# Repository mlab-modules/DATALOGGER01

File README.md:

# DATALOGGER01 - MLAB's Versatile processor module

The DATALOGGER01 is a versatile electronic module designed by MLAB, containing an ATmega1284p processor. The module is programmable in the Arduino IDE and compatible with a variety of development environments and programming languages.

One of the significant features of this module is an SD card slot, a convenient provision for data logging from the processor. With a built-in battery holder, the module ensures uninterrupted operation without reliance on an external power supply.

The DATALOGGER01 exhibits a range of applications, thanks to its I2C, UART, ADC input, and GPIO pins. Additionally, it's furnished with a power switch to effectively manage power consumption of connected devices.

Setting it apart, the module includes an EEPROM AT23CS64, containing a unique serial number to distinguish logs from different DATALOGGER01-based devices. Moreover, it comprises a PCF85263 RTC circuit, with the option to connect a backup battery.

## Key Features:
- **Processor:** [ATmega1284p](https://en.wikipedia.org/wiki/Atmel_AVR#ATmega)
- **Interoperability:** Compatibility with Arduino and supports a range of other development platforms and programming languages.
- **Data Logging:** An SD Card Slot for extensive data storage.
- **Power Management:** Self-sufficient with an integrated battery holder.
- **Connectivity Options:** Diverse interfacing options with I2C, UART, ADC input, and GPIO pins.
- **Energy Efficiency:** Onboard power switch for managing external devices' power consumption.
- **Unique Identification:** Inbuilt [EEPROM AT23CS64](https://www.mouser.com/datasheet/2/268/doc0180-1353557.pdf) with a unique serial number.
- **Real-Time Tracking:** Inclusion of a [PCF85263](https://www.nxp.com/docs/en/data-sheet/PCF85263A.pdf) RTC circuit with backup battery connectivity.

## Potential Use Cases:
- **Data Collection:** Can collect, store, and analyze data from various sensors and devices.
- **Remote Monitoring:** Can be incorporated into IoT systems for remote data collection and monitoring.
- **Autonomous Systems:** Suitable for devices needing independent functioning.
- **Space Research:** Applicable as data loggers and locator devices for stratospheric balloons.

## In Action:
- The DATALOGGER01 module has proven its efficacy in:
   - **[GEODOS01](https://www.ust.cz/UST-dosimeters/GEODOS/)**: A fully autonomous scintillation detector incorporating LoRa IoT, operating without human intervention.
   - **FÍK stratospherics balloons Avionics**: DATALOGGER1 played a important role as a data logger and locator in the stratospheric balloons' avionics organized by [ODZ ÚJF](http://www.ujf.cas.cz/cs/oddeleni/oddeleni-dozimetrie-zareni/vyzkum/lety-fik/).

## Schematics

## Useful Links:
- [ATmega1284p](https://en.wikipedia.org/wiki/Atmel_AVR#ATmega) - Wikipedia
- [ARDUINO Programming Environment](https://www.arduino.cc/) - Official Arduino Site
- [EEPROM AT23CS64](https://www.mouser.com/datasheet/2/268/doc0180-1353557.pdf) - Mouser Electronics
- [PCF85263](https://www.nxp.com/docs/en/data-sheet/PCF85263A.pdf) - NXP Semiconductors

Discover the potential of DATALOGGER01 module and utilize it for your projects!

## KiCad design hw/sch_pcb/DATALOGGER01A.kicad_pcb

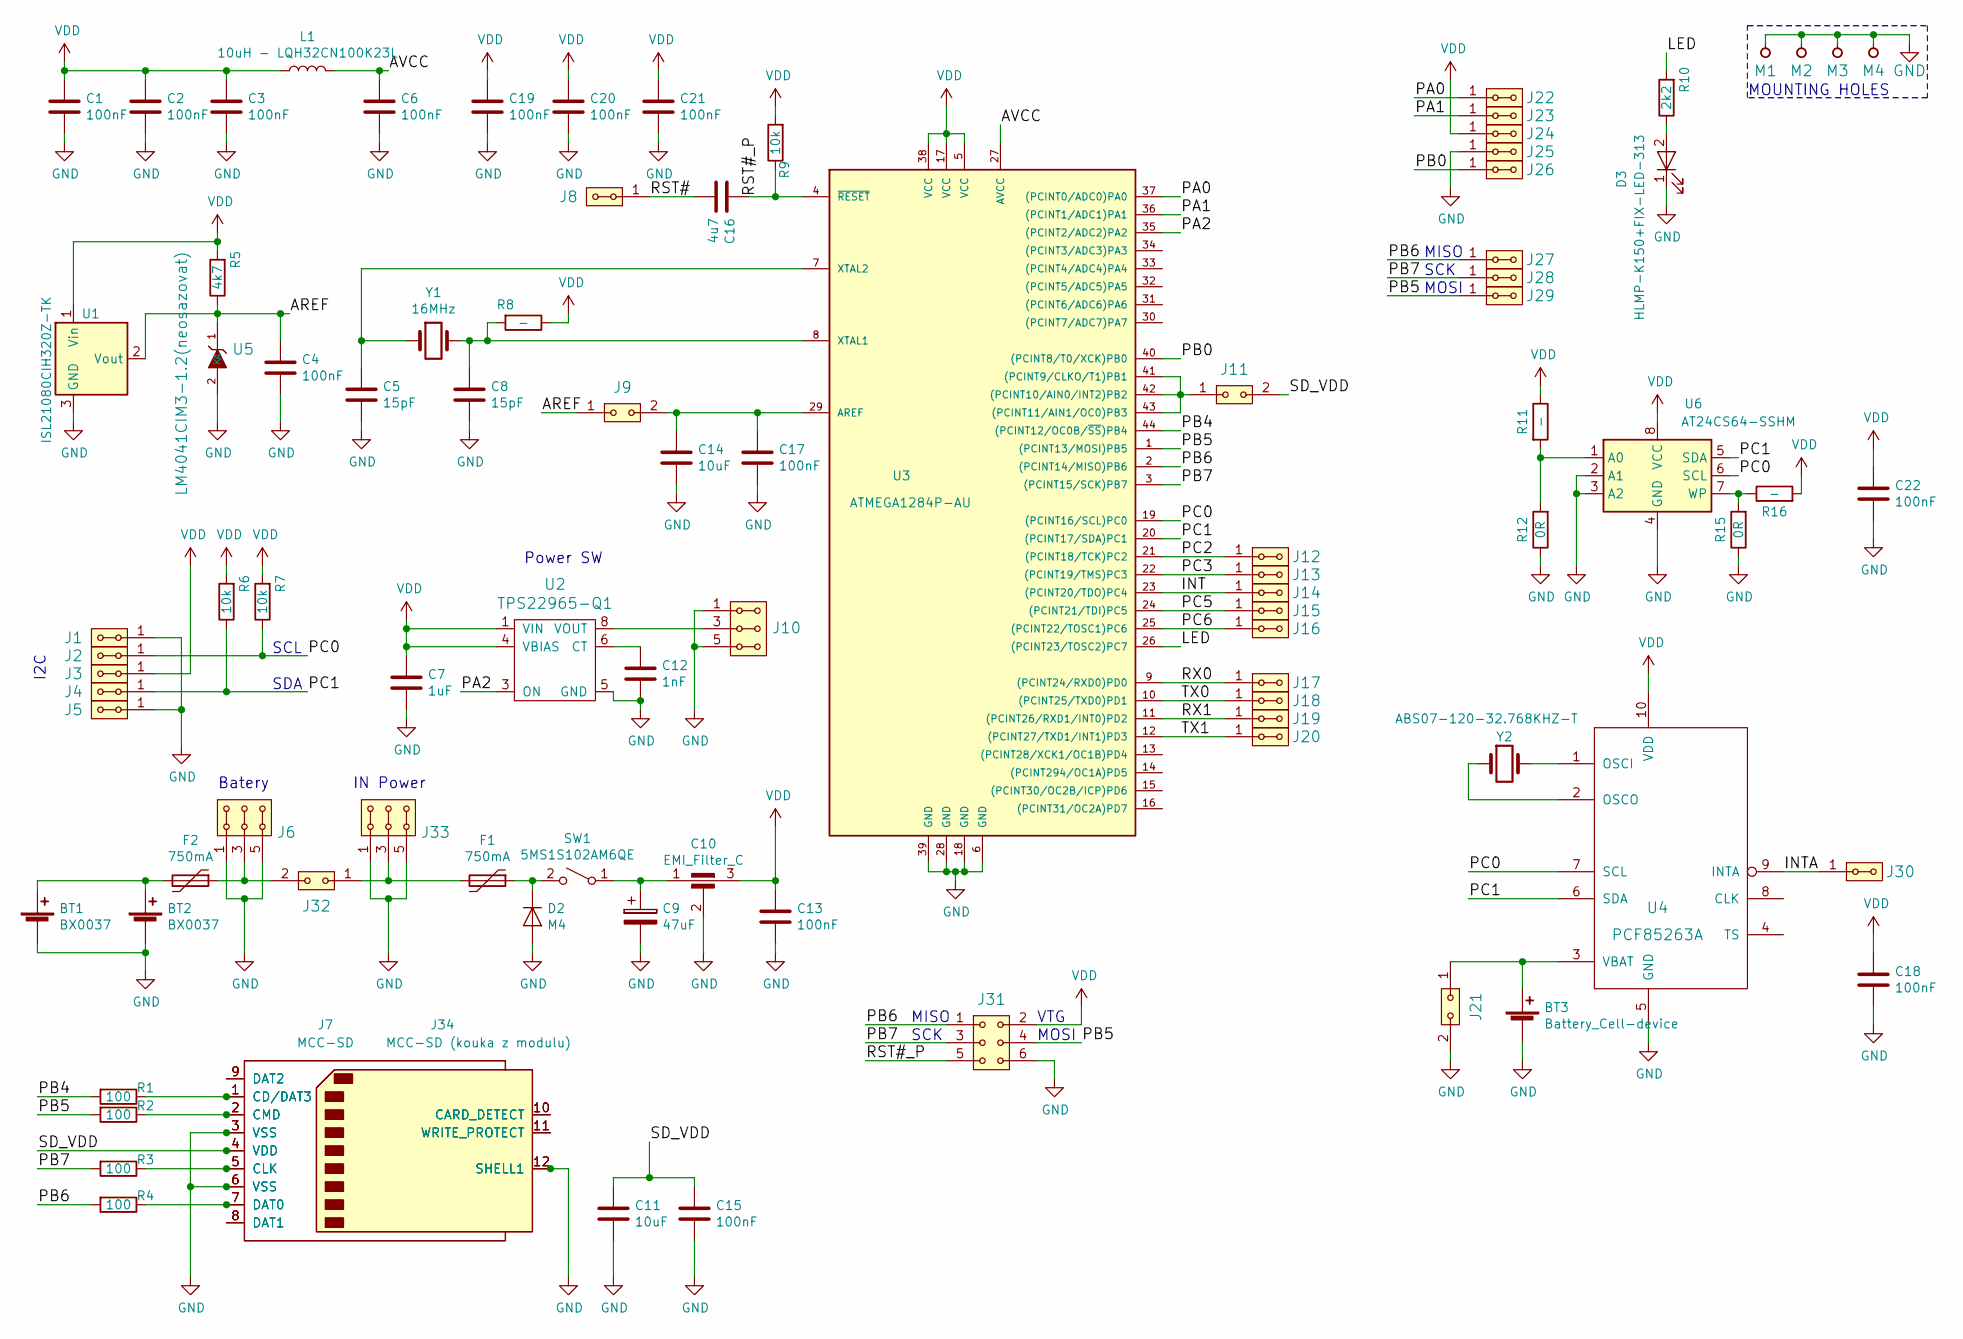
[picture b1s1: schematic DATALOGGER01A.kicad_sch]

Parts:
BT1, BT2: BX0037
BT3: Battery_Cell-device; CH28-2032
C1, C2, C3, C4, C6, C13, C15, C17, C18, C19, C20, C21, C22: 100nF; SMD-0805
C5, C8: 15pF; SMD-0805
C7: 1uF; SMD-0805
C9: 47uF; TantalC_SizeC_Reflow
C10: EMI_Filter_C; FIR1
C11, C14: 10uF; SMD-0805
C12: 1nF; SMD-0805
C16: 4u7; SMD-0805
D2: M4; SMA_Standard
D3: HLMP-K150+FIX-LED-313; FIX-LED-313
F1, F2: 750mA; 1812
J1, J2, J3, J4, J5, J8, J12, J13, J14, J15, J16, J17, J18, J19, J20, J22, J23, J24, J25, J26, J27, J28, J29, J30: HEADER_2x01_PARALLEL; Straight_2x01
J6, J10, J33: HEADER_2x03_PARALLEL; Straight_2x03
J7: MCC-SD; SD_TE_2041021
J9, J11, J21, J32: HEADER_2x01; Straight_2x01
J31: HEADER_2x03; Straight_2x03
J34: MCC-SD (kouka z modulu); MCC-SD
L1: 10uH - LQH32CN100K23L; SMD-1210
M1, M2, M3, M4: HOLE; MountingHole_3mm
R1, R2, R3, R4: 100; SMD-0805
R5: 4k7; SMD-0805
R6, R7, R9: 10k; SMD-0805
R8, R11, R16: -; SMD-0805
R10: 2k2; SMD-0805
R12, R15: 0R; SMD-0805
SW1: 5MS1S102AM6QE
U1: ISL21080CIH320Z-TK; SOT-23
U2: TPS22965-Q1; WSON-8-1EP_2x2mm_P0.5mm_EP0.9x1.6mm_ThermalVias
U3: ATMEGA1284P-AU; TQFP-44_10x10mm_P0.8mm
U4: PCF85263A; TSSOP-10_3x3mm_Pitch0.5mm
U5: LM4041CIM3-1.2(neosazovat); SOT-23
U6: AT24CS64-SSHM; SOIC-8_3.9x4.9mm_P1.27mm
Y1: 16MHz; Crystal_HC49-U_Vertical
Y2: ABS07-120-32.768KHZ-T; ABS07

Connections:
/AREF: C4.1, J9.1, R5.1, U1.2 (Vout), U5.1 (K)
/AVCC: C6.1, L1.2, U3.27 (AVCC)
/INT: J14.1, J14.2, U3.23 ((PCINT20/TDO)PC4)
/INTA: J30.1, J30.2, U4.9 (INTA)
/LED: R10.2, U3.26 ((PCINT23/TOSC2)PC7)
/PA0: J22.1, J22.2, U3.37 ((PCINT0/ADC0)PA0)
/PA1: J23.1, J23.2, U3.36 ((PCINT1/ADC1)PA1)
/PA2: U2.3 (ON), U3.35 ((PCINT2/ADC2)PA2)
/PB0: J26.1, J26.2, U3.40 ((PCINT8/T0/XCK)PB0)
/PB4: R1.2, U3.44 ((PCINT12/OC0B/~SS)PB4)
/PB5: J29.1, J29.2, J31.4, R2.2, U3.1 ((PCINT13/MOSI)PB5)
/PB6: J27.1, J27.2, J31.1, R4.2, U3.2 ((PCINT14/MISO)PB6)
/PB7: J28.1, J28.2, J31.3, R3.2, U3.3 ((PCINT15/SCK)PB7)
/PC0: J2.1, J2.2, R7.1, U3.19 ((PCINT16/SCL)PC0), U4.7 (SCL), U6.6 (SCL)
/PC1: J4.1, J4.2, R6.1, U3.20 ((PCINT17/SDA)PC1), U4.6 (SDA), U6.5 (SDA)
/PC2: J12.1, J12.2, U3.21 ((PCINT18/TCK)PC2)
/PC3: J13.1, J13.2, U3.22 ((PCINT19/TMS)PC3)
/PC5: J15.1, J15.2, U3.24 ((PCINT21/TDI)PC5)
/PC6: J16.1, J16.2, U3.25 ((PCINT22/TOSC1)PC6)
/RST#: C16.2, J8.1, J8.2
/RST#_P: C16.1, J31.5, R9.1, U3.4 (~RESET)
/RX0: J17.1, J17.2, U3.9 ((PCINT24/RXD0)PD0)
/RX1: J19.1, J19.2, U3.11 ((PCINT26/RXD1/INT0)PD2)
/SD_VDD: C11.1, C15.1, J7.4 (VDD), J11.2, J34.4 (VDD)
/TX0: J18.1, J18.2, U3.10 ((PCINT25/TXD0)PD1)
/TX1: J20.1, J20.2, U3.12 ((PCINT27/TXD1/INT1)PD3)
GND: BT1.2 (-), BT2.2 (-), BT3.2 (-), C1.2, C2.2, C3.2, C4.2, C5.2, C6.2, C7.2, C8.2, C9.2, C10.2, C11.2, C12.2, C13.2, C14.2, C15.2, C17.2, C18.2, C19.2, C20.2, C21.2, C22.2, D2.2 (A), D3.1 (K), J1.1, J1.2, J5.1, J5.2, J6.1, J6.2, J6.5, J6.6, J7.3 (VSS), J7.6 (VSS), J7.12 (SHELL1), J10.1, J10.2, J10.5, J10.6, J21.2, J25.1, J25.2, J31.6, J33.1, J33.2, J33.5, J33.6, J34.3 (VSS), J34.6 (VSS), J34.12 (SHELL1), M1.1, M2.1, M3.1, M4.1, R12.1, R15.1, U1.3 (GND), U2.5 (GND), U2.9, U3.6 (GND), U3.18 (GND), U3.28 (GND), U3.39 (GND), U4.5 (GND), U5.2 (A), U6.2 (A1), U6.3 (A2), U6.4 (GND)
unnamed: BT1.1 (+), BT2.1 (+), F2.2
unnamed: BT3.1 (+), J21.1, U4.3 (VBAT)
unnamed: C5.1, U3.7 (XTAL2), Y1.1
unnamed: C8.1, R8.2, U3.8 (XTAL1), Y1.2
unnamed: C9.1, C10.1, SW1.1 (A)
unnamed: C12.1, U2.6 (CT)
unnamed: C14.1, C17.1, J9.2, U3.29 (AREF)
unnamed: D2.1 (K), F1.1, SW1.2 (B)
unnamed: D3.2 (A), R10.1
unnamed: F1.2, J32.1, J33.3, J33.4
unnamed: F2.1, J6.3, J6.4, J32.2
unnamed: J10.3, J10.4, U2.7 (VOUT), U2.8 (VOUT)
unnamed: J11.1, U3.41 ((PCINT9/CLKO/T1)PB1), U3.42 ((PCINT10/AIN0/INT2)PB2), U3.43 ((PCINT11/AIN1/OC0)PB3)
unnamed: J7.1 (CD/DAT3), J34.1 (CD/DAT3), R1.1
unnamed: J7.2 (CMD), J34.2 (CMD), R2.1
unnamed: J7.5 (CLK), J34.5 (CLK), R3.1
unnamed: J7.7 (DAT0), J34.7 (DAT0), R4.1
unnamed: J7.8 (DAT1), J34.8 (DAT1)
unnamed: J7.9 (DAT2), J34.9 (DAT2)
unnamed: J7.10 (CARD_DETECT), J34.10 (CARD_DETECT)
unnamed: J7.11 (WRITE_PROTECT), J34.11 (WRITE_PROTECT)
unnamed: R11.2, R12.2, U6.1 (A0)
unnamed: R15.2, R16.1, U6.7 (WP)
unnamed: U4.1 (OSCI), Y2.2
unnamed: U4.2 (OSCO), Y2.1
VDD: C1.1, C2.1, C3.1, C7.1, C10.3, C13.1, C18.1, C19.1, C20.1, C21.1, C22.1, J3.1, J3.2, J24.1, J24.2, J31.2, L1.1, R5.2, R6.2, R7.2, R8.1, R9.2, R11.1, R16.2, U1.1 (Vin), U2.1 (VIN), U2.2 (VIN), U2.4 (VBIAS), U3.5 (VCC), U3.17 (VCC), U3.38 (VCC), U4.10 (VDD), U6.8 (VCC)

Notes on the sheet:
MISO
VTG
SCK
Batery
I2C
IN Power
MOSI
Power SW
SDA
MOUNTING HOLES
SCL

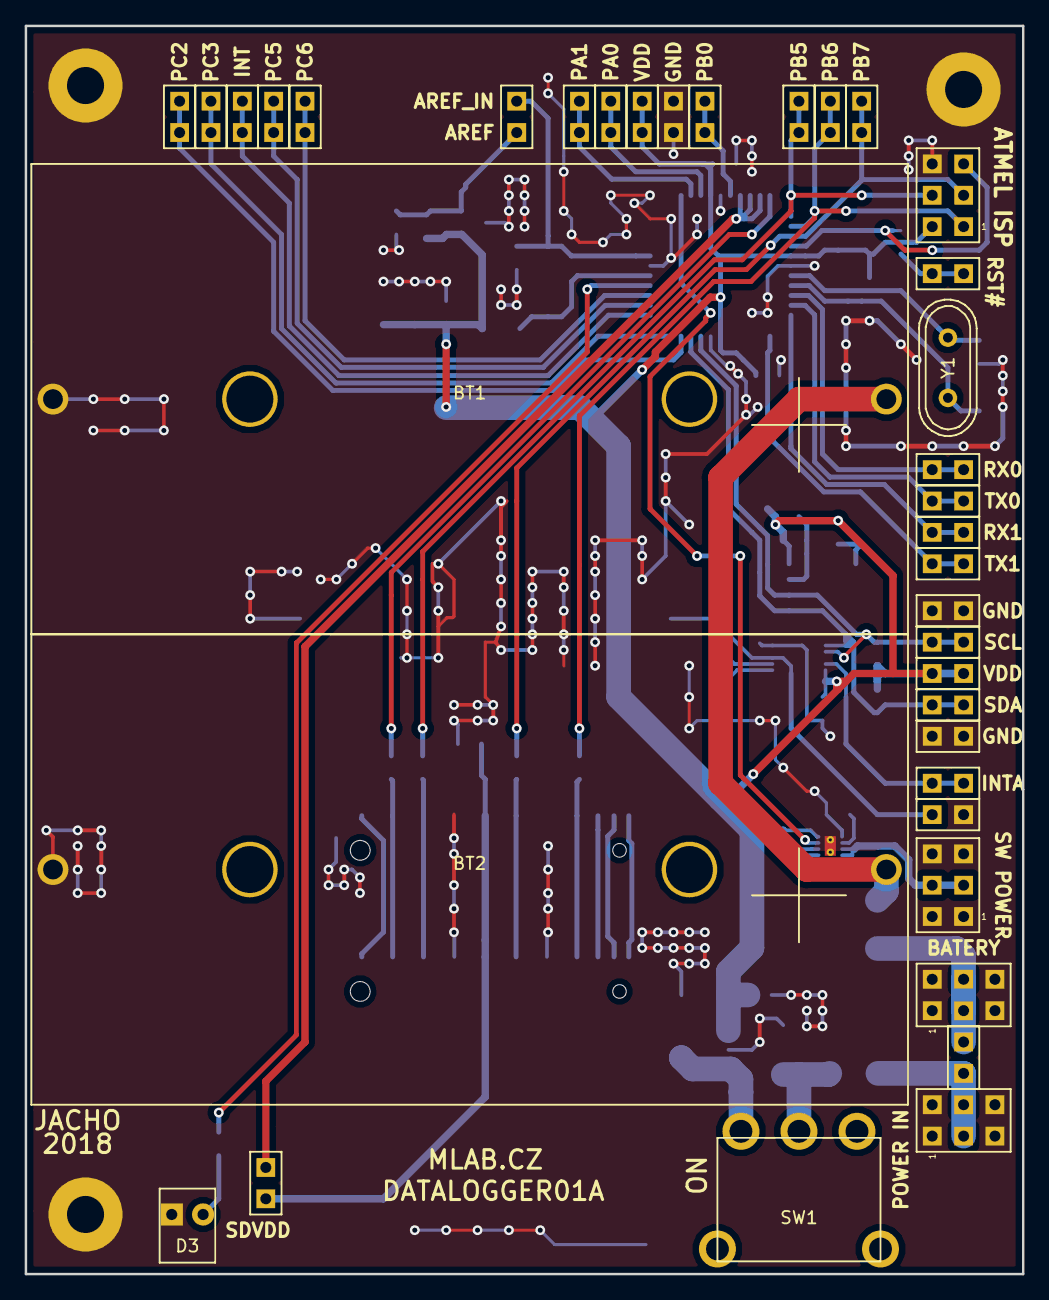
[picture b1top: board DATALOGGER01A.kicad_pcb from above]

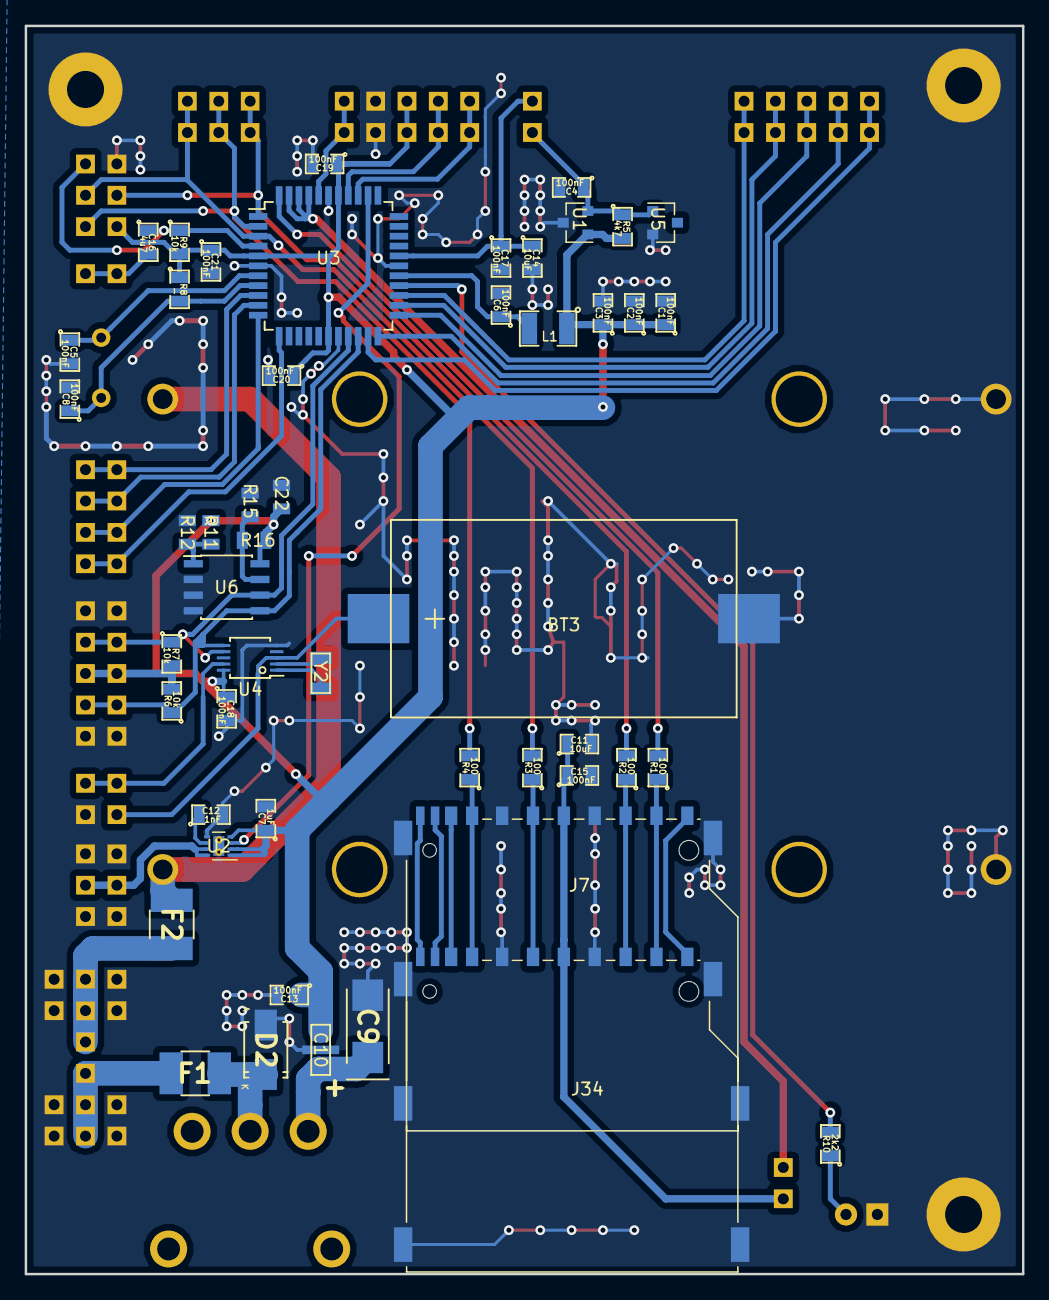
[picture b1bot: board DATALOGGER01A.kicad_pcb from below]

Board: 2 copper layers, 80.8 x 101.1 mm, 90 parts (50 on the bottom side), 53 nets.

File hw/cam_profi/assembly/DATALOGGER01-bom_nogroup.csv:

Component,Description,Part,References,Value,Footprint,Quantity Per PCB,Datasheet,ust_id
1,,Battery_Cell-device,BT1BT2,BX0037,BX0037,2,,5c70984412875079b91f87ed
2,,Battery_Cell-device,BT3,Battery_Cell-device,CH28-2032,1,,5c70984412875079b91f87ec
3,,C-device,C5C8,15pF,SMD-0805,2,,5c70984712875079b91f8b32
4,,C-device,C12,1nF,SMD-0805,1,,5c70984712875079b91f8b45
5,,C-device,C1C2C3C4C6C13C15C17C18C19C20C21C22,100nF,SMD-0805,13,,5c70984712875079b91f8b4c
6,,C-device,C7,1uF,SMD-0805,1,,5c70984712875079b91f8b50
7,,C-device,C16,4u7,SMD-0805,1,,5c70984712875079b91f8b52
8,,C-device,C11C14,10uF,SMD-0805,2,,5c70984812875079b91f8bbd
9,,CP-device,C9,47uF,TantalC_SizeC_Reflow,1,,5c70984412875079b91f8867
10,,EMI_Filter_C-device,C10,EMI_Filter_C,FIR1,1,http://www.murata.com/~/media/webrenewal/support/library/cat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,
11,,LED-device,D3,HLMP-K150+FIX-LED-313,FIX-LED-313,1,,5c70984712875079b91f8b67
12,,D-device,D2,M4,SMA_Standard,1,,5c70984512875079b91f88ac
13,,Polyfuse-device,F1F2,750mA,1812,2,,5c70984512875079b91f88d2
14,,HEADER_2x01-MLAB_HEADER,J9J11J21J32,HEADER_2x01,Straight_2x01,4,,
15,,HEADER_2x01_PARALLEL-MLAB_HEADER,J1J2J3J4J5J8J12J13J14J15J16J17J18J19J20J22J23J24J25J26J27J28J29J30,HEADER_2x01_PARALLEL,Straight_2x01,24,,
16,,HEADER_2x03-MLAB_HEADER,J31,HEADER_2x03,Straight_2x03,1,,
17,,HEADER_2x03_PARALLEL-MLAB_HEADER,J6J10J33,HEADER_2x03_PARALLEL,Straight_2x03,3,,
18,,SD_Card-Connector,J7,MCC-SD,SD_TE_2041021,1,http://portal.fciconnect.com/Comergent//fci/drawing/10067847.pdf,5c70984412875079b91f87f2
19,,SD_Card-Connector,J34,MCC-SD (kouka z modulu),MCC-SD,1,http://portal.fciconnect.com/Comergent//fci/drawing/10067847.pdf,
20,,L-device,L1,10uH - LQH32CN100K23L,SMD-1210,1,,5c70984412875079b91f87ff
21,,R-device,R12R15,0R,SMD-0805,2,,5c70984512875079b91f896b
22,,R-device,R1R2R3R4,100,SMD-0805,4,,5c70984512875079b91f8977
23,,R-device,R10,2k2,SMD-0805,1,,5c70984612875079b91f8990
24,,R-device,R5,4k7,SMD-0805,1,,5c70984612875079b91f8995
25,,R-device,R6R7R9,10k,SMD-0805,3,,5c70984612875079b91f899f
26,,R-device,R8R11R16,-,SMD-0805,3,,
27,Single Pole Single Throw (SPST) switch,SW_SPST,SW1,5MS1S102AM6QE,5MS1S102AM6QE,1,~,5c70984712875079b91f8b66
28,"I2C Serial EEPROM, 64Kb (8192x8) with Unique Serial Number, SO8",AT24CS64-SSHM,U6,AT24CS64-SSHM,SOIC-8_3.9x4.9mm_P1.27mm,1,http://ww1.microchip.com/downloads/en/DeviceDoc/Atmel-8870-S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,5c70984712875079b91f8b99
29,,ATMEGA1284P-AU-atmel,U3,ATMEGA1284P-AU,TQFP-44_10x10mm_P0.8mm,1,http://www.atmel.com/Images/Atmel-8272-8-bit-AVR-microcontro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,5c70984412875079b91f888e
30,,ISL21070CIH320Z-TK-references,U1,ISL21080CIH320Z-TK,SOT-23,1,http://www.intersil.com/content/dam/Intersil/documents/fn75/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,5c70984712875079b91f8b79
31,,LM4041CIM3-1.2-MLAB_D,U5,LM4041CIM3-1.2(neosazovat),SOT-23,1,,
32,,PCF85263A-MLAB_IO,U4,PCF85263A,TSSOP-10_3x3mm_Pitch0.5mm,1,,5c70984612875079b91f8a0c
33,,TPS22965-Q1-MLAB_IO,U2,TPS22965-Q1,WSON-8-1EP_2x2mm_P0.5mm_EP0.9x1.6mm_ThermalVias,1,,5c70984712875079b91f8b78
34,Two pin crystal,Crystal,Y1,16MHz,Crystal_HC49-U_Vertical,1,~,5c70984712875079b91f8b10
35,,Crystal-device,Y2,ABS07-120-32.768KHZ-T,ABS07,1,,5c70984712875079b91f8b1b

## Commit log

2018-06-06 [MLABweb] Documentaion edits; DATALOGGER01A
2018-06-06 Schema noveho modulu
2018-06-08 Edit schema
2018-06-13 Editace schema
2018-06-15 edit
2018-08-01 Pridani obvodu pro SSN. Oprava resetu.
2018-08-05 Editace modulu
2020-10-28 Fix licence and repository cleanup.
2020-10-28 Documentation improvement. KiCAD files upgraded to new version.
2020-10-28 Crop images.
2021-02-24 Doplneni soucastek na osazovani
2021-02-24 Doplnění součástek pro osazení
2021-08-27 Edit SCH
2021-12-29 Update schematics and title block.
2022-02-17 MLAB web edit.
2022-04-06 automated commit; add github actions
2022-04-06 Update actions products
2022-08-14 Fix titleblock version.
2022-08-19 Update title blocks Place board to the center of page.
2022-08-19 Set up coordinates origin in left bottom corner of board.
2022-08-19 Remove old github actions.
2023-05-24 Update metadata files
2023-05-24 Update workflow files
2023-07-05 automated commit; rename source files to new naming convence
2023-09-16 Update image to image_title
2023-09-16 Update status

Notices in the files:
hw/sch_pcb/DATALOGGER01A.kicad_pcb:
GPL 3.0
hw/sch_pcb/DATALOGGER01A.kicad_sch:
GPL 3
